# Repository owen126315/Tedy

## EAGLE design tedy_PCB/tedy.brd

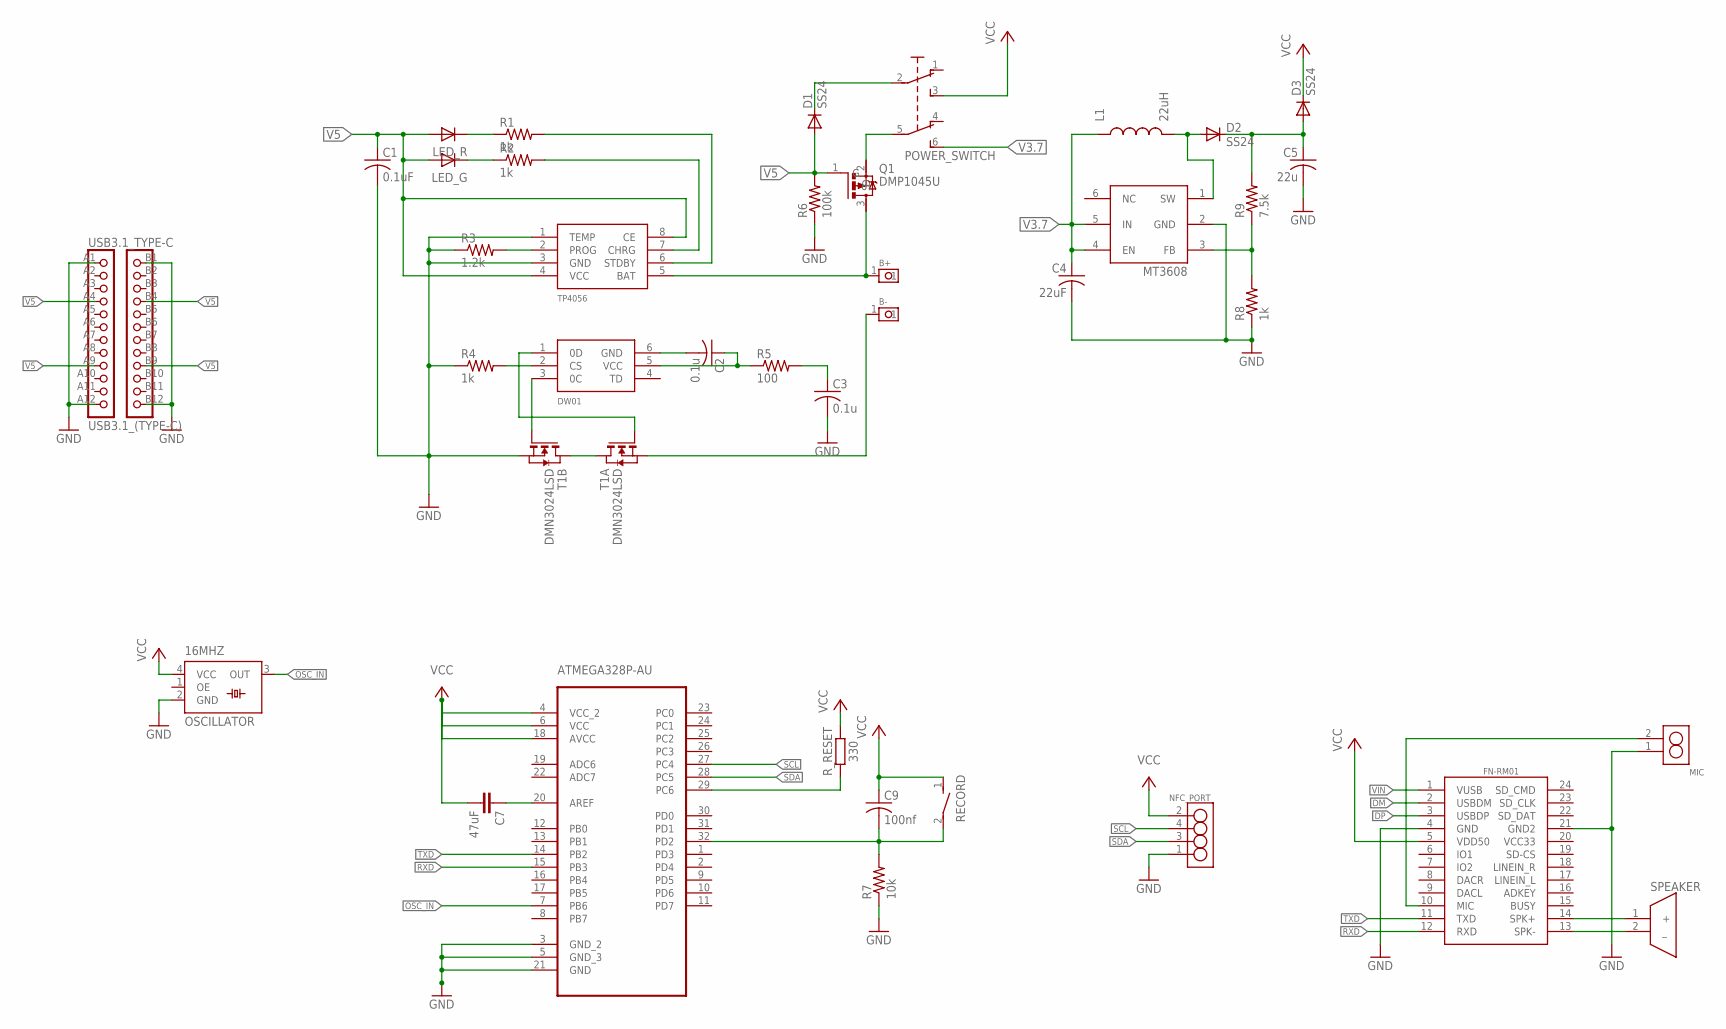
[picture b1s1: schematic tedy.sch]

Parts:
16MHZ: OSCILLATOR; OSCILLATOR_(3.2*2.5)
ATMEGA328P-AU: ATMEGA328P-AU; QFP80P900X900X120-32N
B+: B+; PIN_1
B-: B-; PIN_1
C1: 0.1uF; C0805
C2, C3: 0.1u; C0805
C4: 22uF; C0805
C5: 22u; C0805
C7: 47uF; C0805
C9: 100nf; C0805K
D1, D2, D3: SS24
DW01: DW01; SOT23-6
FN-RM01: FN-RM01
L1: 22uH; 4D28
LED_: 2_COLOUR_LED
MIC: CONNECTOR_1.5MM_THROUGH_HOLE_(2_PIN)
MT3608: MT3608; SOT23-6
NFC_PORT: PN532
POWER_SWITCH: 6PIN_SWITCH
Q1: DMP1045U; SOT23-3
R1, R2, R4, R8: 1k; R0805
R3: 1.2k; R0805
R5: 100; R0805
R6: 100k; R0805
R7: 10k; R0805
R9: 7.5k; R0805
RECORD: PUSH_BUTTON(SIDE)
R_RESET: 330; M0805
SPEAKER: SPEAKER
T1: DMN3024LSD; TSSOP-8
TP4056: TP4056; SOP-8
USB3.1_TYPE-C: USB3.1_(TYPE-C)

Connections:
DM: FN-RM01.2 (USBDM)
DP: FN-RM01.3 (USBDP)
GND: 16MHZ.2 (GND), ATMEGA328P-AU.3 (GND_2), ATMEGA328P-AU.5 (GND_3), ATMEGA328P-AU.21 (GND), C1.2, C3.2, C4.2, C5.2, FN-RM01.4 (GND), FN-RM01.21 (GND2), MIC.1, MT3608.2 (GND), NFC_PORT.1 (4), R3.1, R4.1, R6.1, R7.1, R8.1, T1.6 (S), T1.7 (S), TP4056.1 (TEMP), TP4056.3 (GND), USB3.1_TYPE-C.A1, USB3.1_TYPE-C.A12, USB3.1_TYPE-C.B1, USB3.1_TYPE-C.B12
unnamed: ATMEGA328P-AU.29 (PC6), R_RESET.2
unnamed: LED_.1, R1.1
unnamed: LED_.3 (1), R2.1
unnamed: R3.2, TP4056.2 (PROG)
unnamed: R1.2, TP4056.6 (STDBY)
unnamed: DW01.2 (CS), R4.2
unnamed: R2.2, TP4056.7 (CHRG)
unnamed: DW01.1 (0D), T1.4 (G)
unnamed: DW01.3 (0C), T1.5 (G)
unnamed: T1.1 (D), T1.8 (D)
unnamed: C2.2, DW01.6 (GND)
unnamed: C2.1, DW01.5 (VCC), R5.1
unnamed: B+.1, Q1.3 (D), TP4056.5 (BAT)
unnamed: C3.1, R5.2
unnamed: B-.1, T1.2 (S), T1.3 (S)
unnamed: MT3608.3 (FB), R8.2, R9.1
unnamed: D1.2 (C), POWER_SWITCH.2
unnamed: C5.1, D2.2 (C), D3.1 (A), R9.2
unnamed: D2.1 (A), L1.P$2 (2), MT3608.1 (SW)
unnamed: ATMEGA328P-AU.20 (AREF), C7.1
unnamed: FN-RM01.14 (SPK+), SPEAKER.1 (+)
unnamed: FN-RM01.13 (SPK-), SPEAKER.2 (_)
unnamed: FN-RM01.10 (MIC), MIC.2
unnamed: ATMEGA328P-AU.32 (PD2), C9.2, R7.2, RECORD.2
OSC_IN: 16MHZ.3 (OUT), ATMEGA328P-AU.7 (PB6)
RXD: ATMEGA328P-AU.15 (PB3), FN-RM01.12 (RXD)
SCL: ATMEGA328P-AU.27 (PC4), NFC_PORT.4 (2)
SDA: ATMEGA328P-AU.28 (PC5), NFC_PORT.3
TXD: ATMEGA328P-AU.14 (PB2), FN-RM01.11 (TXD)
V3.7: C4.1, L1.P$1 (1), MT3608.4 (EN), MT3608.5 (IN), POWER_SWITCH.5 (P1), POWER_SWITCH.6 (S1), Q1.2 (S)
V5: C1.1, D1.1 (A), LED_.2, LED_.4 (2), Q1.1 (G), R6.2, TP4056.4 (VCC), TP4056.8 (CE), USB3.1_TYPE-C.A4, USB3.1_TYPE-C.A9, USB3.1_TYPE-C.B4, USB3.1_TYPE-C.B9
VCC: 16MHZ.4 (VCC), ATMEGA328P-AU.4 (VCC_2), ATMEGA328P-AU.6 (VCC), ATMEGA328P-AU.18 (AVCC), C7.2, C9.1, D3.2 (C), FN-RM01.5 (VDD50), NFC_PORT.2 (1), POWER_SWITCH.3 (S), RECORD.1, R_RESET.1
VIN: FN-RM01.1 (VUSB)

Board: 2 copper layers, 38 parts (0 on the bottom side), 33 nets, no tracks yet.

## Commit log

2018-09-12 V_1.0
2019-02-16 update on 16-2-2019
2019-02-16 Revert "V_1.0"
    This reverts commit f1c4317fea3934c8b23aac20fa285d5cc6b40cea.
2019-02-22 update on 23/2/2019
2019-04-23 try new branch
2019-04-23 in try 3
2019-04-23 no try.txt
2019-05-04 updated on 5-5-2019
2019-06-07 rm old code
2019-06-07 stm32 code
2019-07-14 stm32f0 version added
